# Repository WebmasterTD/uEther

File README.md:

# uEther

uEther is Ethernet exansion card designed for [Clockwork uConsole](https://www.clockworkpi.com/uconsole).

Based on the microchip LAN9500A USB 2.0 to 10/100 Ethernet Bridge.

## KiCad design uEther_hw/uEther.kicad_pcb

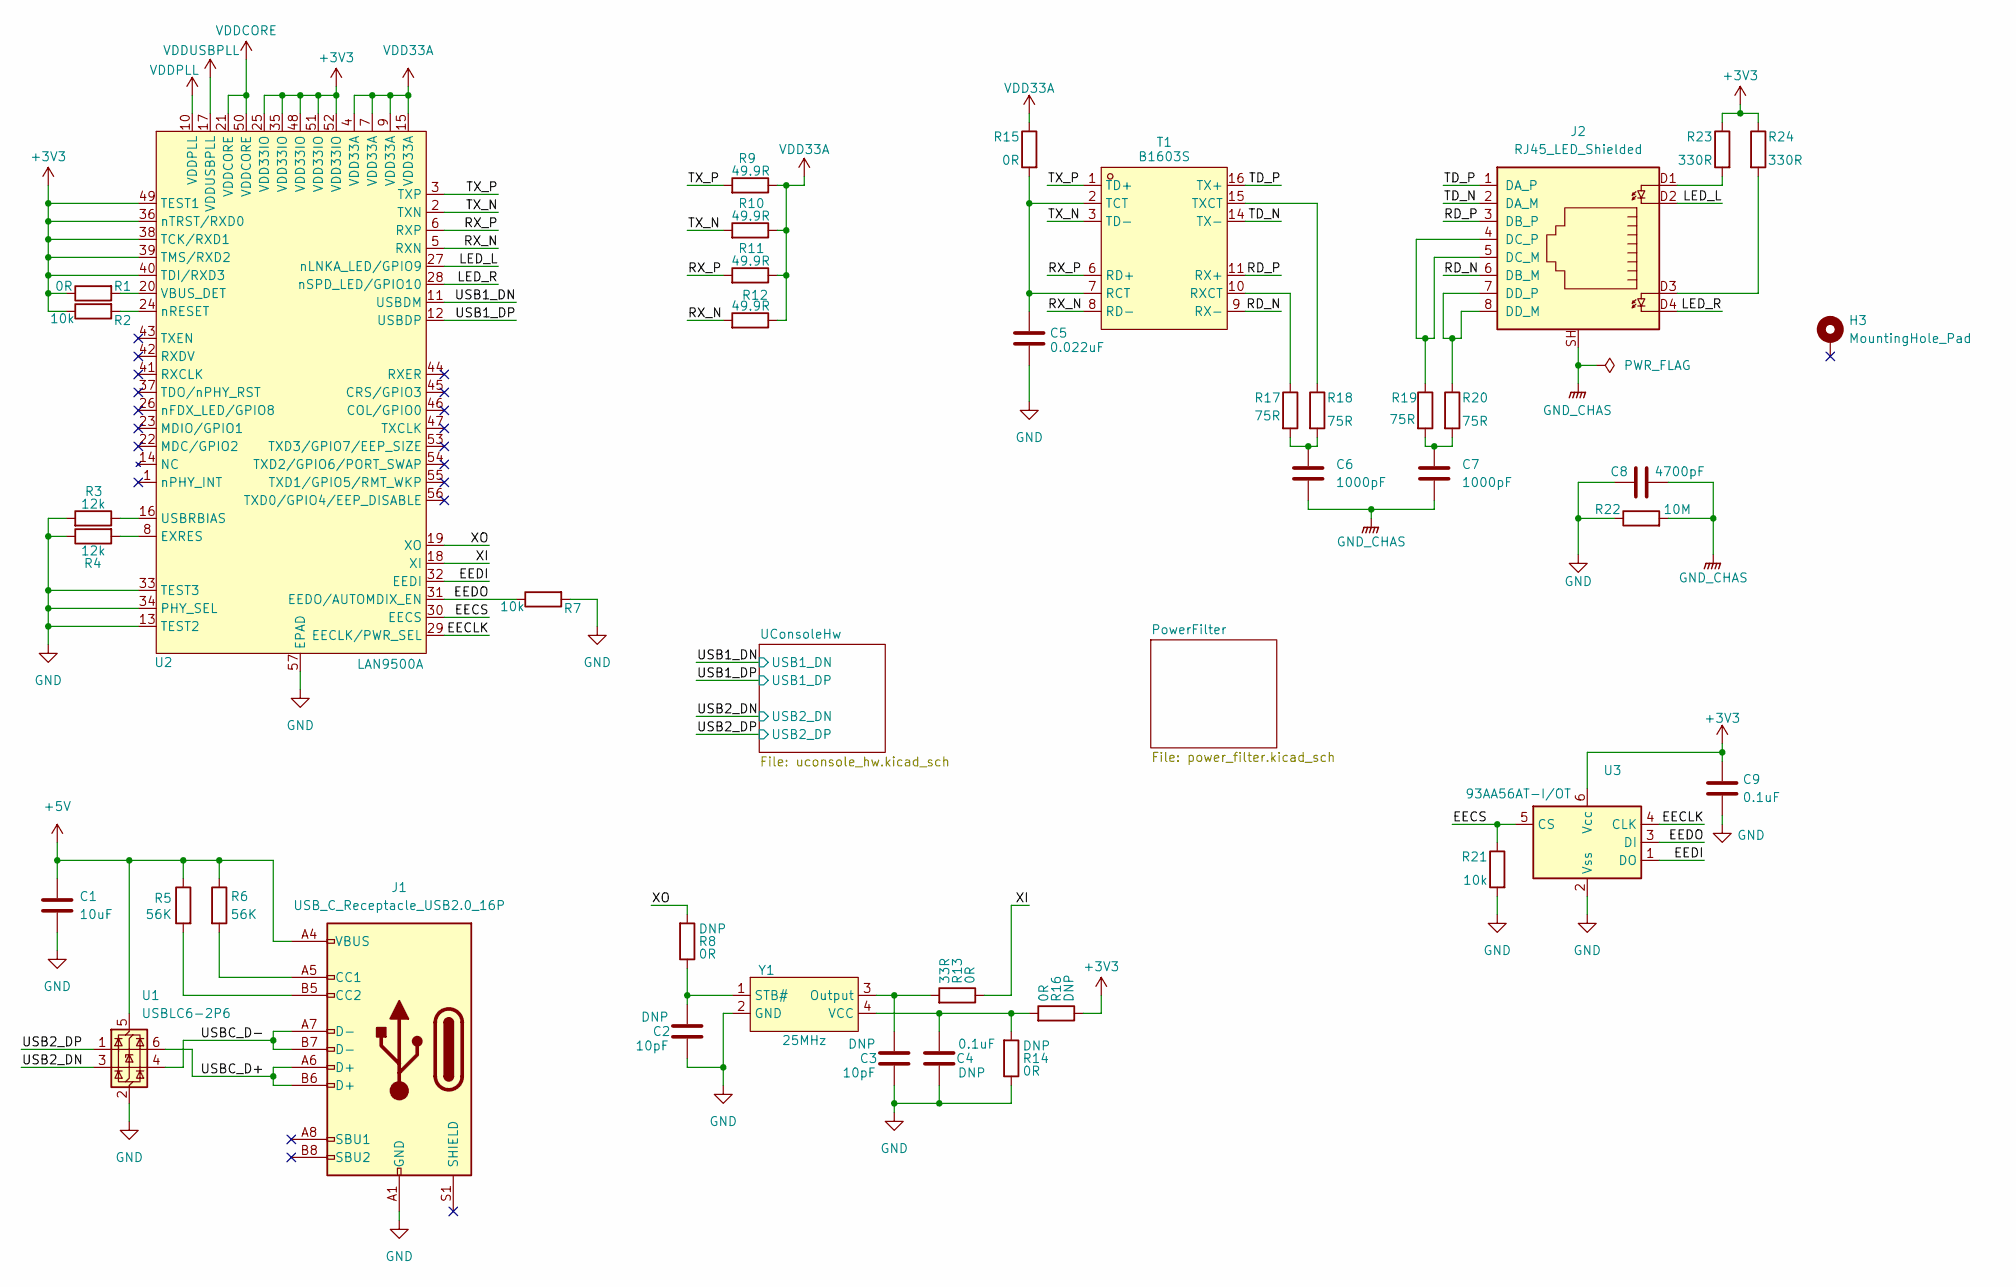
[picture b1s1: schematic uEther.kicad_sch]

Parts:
C1: 10uF; C_0603_1608Metric
C2, C3, C4: C_0603_1608Metric
C5: 0.022uF; C_0603_1608Metric
C6, C7: 1000pF; C_1206_3216Metric
C8: 4700pF; C_0603_1608Metric
C9: 0.1uF; C_0603_1608Metric
H3: MountingHole_Pad; MountingHole_2.2mm_M2_ISO7380_Pad
J1: USB_C_Receptacle_USB2.0_16P; USB_C_Receptacle_G-Switch_GT-USB-7010ASV
J2: RJ45_LED_Shielded; RJ45-005-014-11
R1, R15: 0R; R_0603_1608Metric
R2, R7, R21: 10k; R_0603_1608Metric
R3, R4: 12k; R_0603_1608Metric
R5, R6: 56K; R_0603_1608Metric
R8, R13, R14, R16: R_0603_1608Metric
R9, R10, R11, R12: 49.9R; R_0603_1608Metric
R17, R18, R19, R20: 75R; R_0603_1608Metric
R22: 10M; R_0603_1608Metric
R23, R24: 330R; R_0603_1608Metric
T1: B1603S; SOIC-16W_7.5x12.8mm_P1.27mm; Manufacturer Part B1603S; LCSC Part Name B1603S
U1: USBLC6-2P6; SOT-666
U2: LAN9500A; QFN-56-1EP_8x8mm_P0.5mm_EP5.9x5.9mm_ThermalVias; Manufacturer Part LAN9500A-ABZJ-TR; LCSC Part Name LAN950x USB 2.0 到 10/100 以太网控制器
U3: 93AA56AT-I/OT; SOT-23-6
Y1: 25MHz; Crystal_SMD_3225-4Pin_3.2x2.5mm; Manufacturer Part DSC1001CI2-025.0000T; LCSC Part Name 25MHz ±25ppm 1.8V~3.3V CMOS

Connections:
+3V3: C9.1, R1.1, R2.1, R16.1, R23.1, R24.1, U2.25 (VDD33IO), U2.35 (VDD33IO), U2.36 (nTRST/RXD0), U2.38 (TCK/RXD1), U2.39 (TMS/RXD2), U2.40 (TDI/RXD3), U2.48 (VDD33IO), U2.49 (TEST1), U2.51 (VDD33IO), U2.52 (VDD33IO), U3.6 (Vcc); also elsewhere on the board
+5V: C1.1, J1.A4 (VBUS), J1.A9 (VBUS), J1.B4 (VBUS), J1.B9 (VBUS), R5.1, R6.1, U1.5 (VBUS); also elsewhere on the board
/EECLK: U2.29 (EECLK/PWR_SEL), U3.4 (CLK)
/EECS: R21.1, U2.30 (EECS), U3.5 (CS)
/EEDI: U2.32 (EEDI), U3.1 (DO)
/EEDO: R7.1, U2.31 (EEDO/AUTOMDIX_EN), U3.3 (DI)
/LED_L: J2.D2, U2.27 (nLNKA_LED/GPIO9)
/LED_R: J2.D4, U2.28 (nSPD_LED/GPIO10)
/RD_N: J2.6 (DB_M), T1.9 (RX-)
/RD_P: J2.3 (DB_P), T1.11 (RX+)
/RX_N: R12.2, T1.8 (RD-), U2.5 (RXN)
/RX_P: R11.2, T1.6 (RD+), U2.6 (RXP)
/TD_N: J2.2 (DA_M), T1.14 (TX-)
/TD_P: J2.1 (DA_P), T1.16 (TX+)
/TX_N: R10.2, T1.3 (TD-), U2.2 (TXN)
/TX_P: R9.2, T1.1 (TD+), U2.3 (TXP)
/USB1_DN: U2.11 (USBDM); also elsewhere on the board
/USB1_DP: U2.12 (USBDP); also elsewhere on the board
/USB2_DN: U1.3 (I/O2); also elsewhere on the board
/USB2_DP: U1.1 (I/O1); also elsewhere on the board
/USBC_D+: J1.A6 (D+), J1.B6 (D+), U1.6 (I/O1)
/USBC_D-: J1.A7 (D-), J1.B7 (D-), U1.4 (I/O2)
/XI: R13.1, U2.18 (XI)
/XO: R8.2, U2.19 (XO)
GND: C1.2, C2.2, C3.2, C4.2, C5.2, C8.1, C9.2, J1.A1 (GND), J1.A12 (GND), J1.B1 (GND), J1.B12 (GND), R3.2, R4.1, R7.2, R14.1, R21.2, R22.1, U1.2 (GND), U2.13 (TEST2), U2.33 (TEST3), U2.34 (PHY_SEL), U2.57 (EPAD), U3.2 (Vss), Y1.2 (GND); also elsewhere on the board
GND_CHAS: C6.2, C7.2, C8.2, J2.SH, R22.2
unnamed: C6.1, R17.2, R18.2
unnamed: C7.1, R19.2, R20.2
unnamed: J1.A5 (CC1), R6.2
unnamed: J1.B5 (CC2), R5.2
unnamed: J2.4 (DC_P), J2.5 (DC_M), R19.1
unnamed: J2.7 (DD_P), J2.8 (DD_M), R20.1
unnamed: J2.D1, R23.2
unnamed: J2.D3, R24.2
unnamed: C5.1, R15.2, T1.2 (TCT), T1.7 (RCT)
unnamed: R17.1, T1.10 (RXCT)
unnamed: R18.1, T1.15 (TXCT)
unnamed: R4.2, U2.8 (EXRES)
unnamed: R3.1, U2.16 (USBRBIAS)
unnamed: R1.2, U2.20 (VBUS_DET)
unnamed: R2.2, U2.24 (nRESET)
unnamed: C3.1, R13.2, Y1.3 (Output)
unnamed: C2.1, R8.1, Y1.1 (STB#)
unnamed: C4.1, R14.2, R16.2, Y1.4 (VCC)
VDD33A: R9.1, R10.1, R11.1, R12.1, R15.1, U2.4 (VDD33A), U2.7 (VDD33A), U2.9 (VDD33A), U2.15 (VDD33A); also elsewhere on the board
VDDCORE: U2.21 (VDDCORE), U2.50 (VDDCORE); also elsewhere on the board
VDDPLL: U2.10 (VDDPLL); also elsewhere on the board
VDDUSBPLL: U2.17 (VDDUSBPLL); also elsewhere on the board

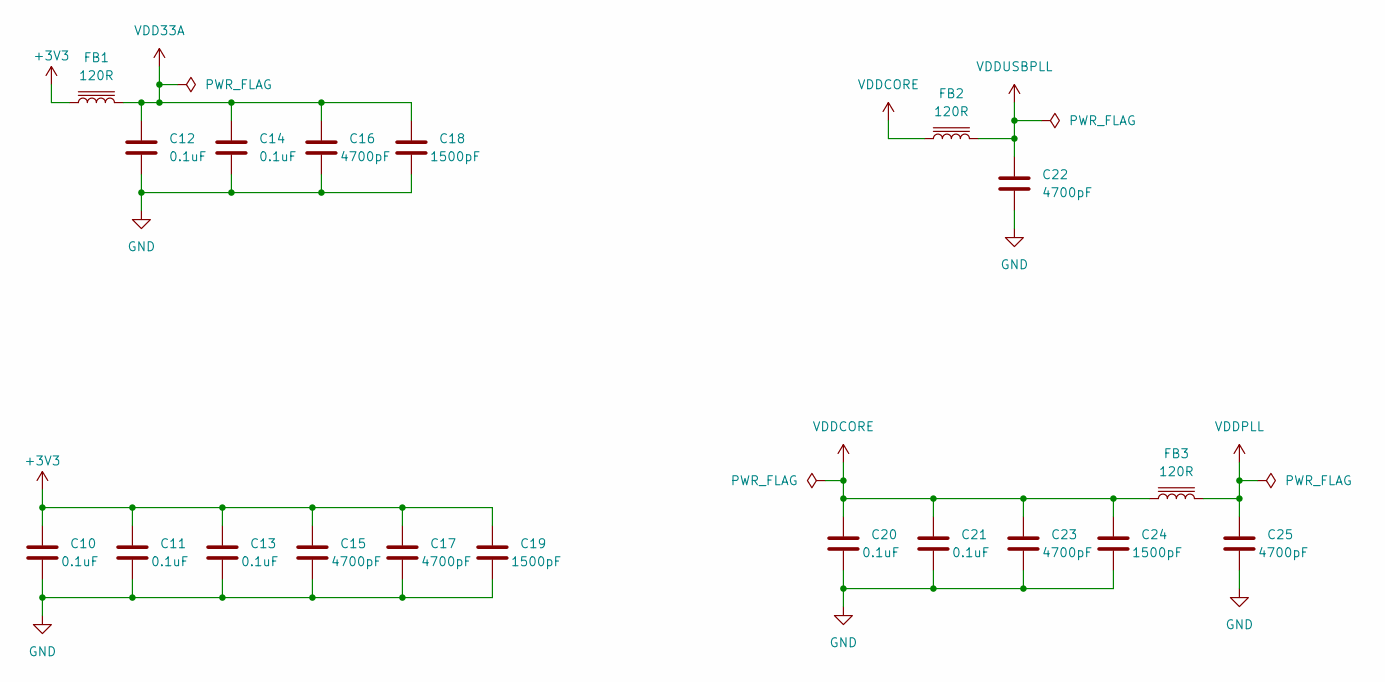
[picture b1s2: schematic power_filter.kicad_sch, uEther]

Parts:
C10, C11, C12, C13, C14, C20, C21: 0.1uF; C_0603_1608Metric
C15, C16, C17, C22, C23, C25: 4700pF; C_0603_1608Metric
C18, C19, C24: 1500pF; C_0603_1608Metric
FB1, FB2, FB3: 120R; L_0603_1608Metric

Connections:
+3V3: C10.1, C11.1, C13.1, C15.1, C17.1, C19.1, FB1.1; also elsewhere on the board
GND: C10.2, C11.2, C12.2, C13.2, C14.2, C15.2, C16.2, C17.2, C18.2, C19.2, C20.2, C21.2, C22.2, C23.2, C24.2, C25.2; also elsewhere on the board
VDD33A: C12.1, C14.1, C16.1, C18.1, FB1.2; also elsewhere on the board
VDDCORE: C20.1, C21.1, C23.1, C24.1, FB2.1, FB3.1; also elsewhere on the board
VDDPLL: C25.1, FB3.2; also elsewhere on the board
VDDUSBPLL: C22.1, FB2.2; also elsewhere on the board

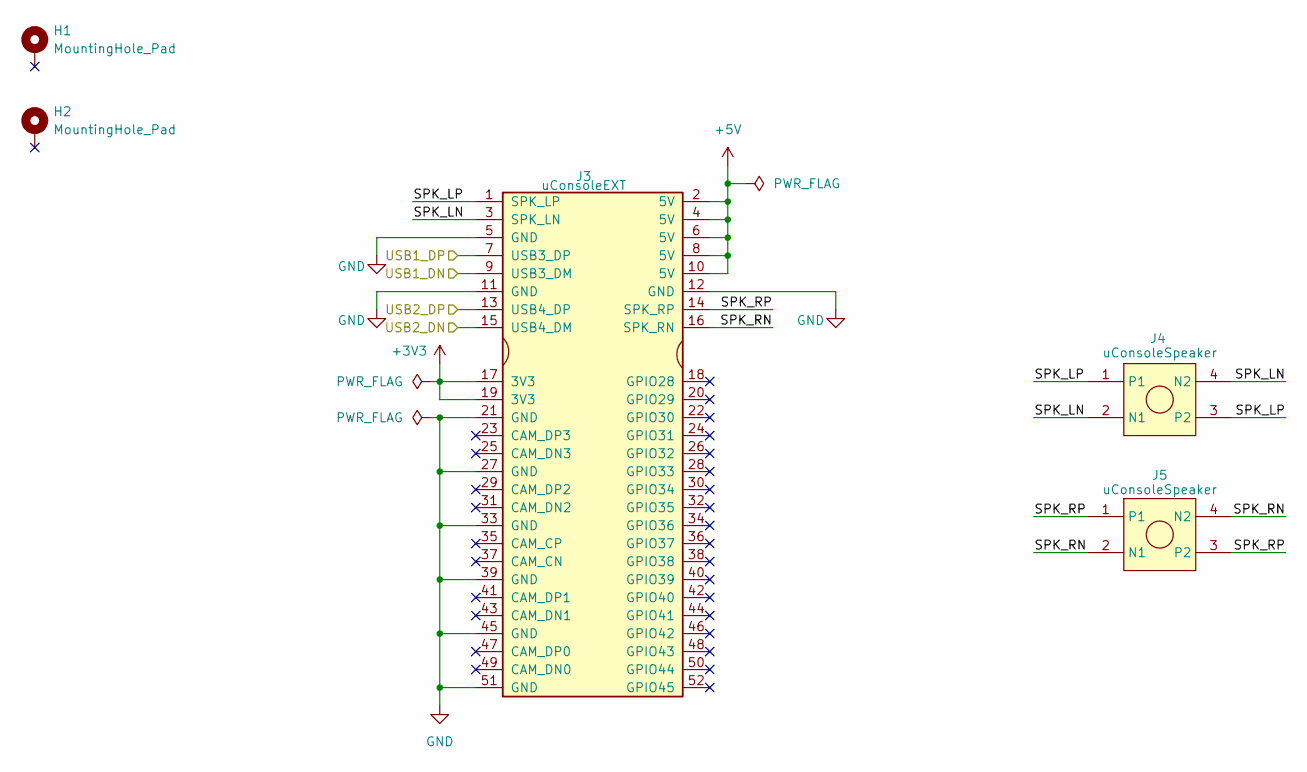
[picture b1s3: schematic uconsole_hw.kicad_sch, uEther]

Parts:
H1, H2: MountingHole_Pad; MountingHole_5mm_Pad_TopOnly
J3: uConsoleEXT; ext
J4, J5: uConsoleSpeaker; speaker

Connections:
+3V3: J3.17 (3V3), J3.19 (3V3); also elsewhere on the board
+5V: J3.2 (5V), J3.4 (5V), J3.6 (5V), J3.8 (5V), J3.10 (5V); also elsewhere on the board
/UConsoleHw/SPK_LN: J3.3 (SPK_LN), J4.2 (N1), J4.4 (N2)
/UConsoleHw/SPK_LP: J3.1 (SPK_LP), J4.1, J4.3 (P2)
/UConsoleHw/SPK_RN: J3.16 (SPK_RN), J5.2 (N1), J5.4 (N2)
/UConsoleHw/SPK_RP: J3.14 (SPK_RP), J5.1, J5.3 (P2)
/USB1_DN: J3.9 (USB3_DM); also elsewhere on the board
/USB1_DP: J3.7 (USB3_DP); also elsewhere on the board
/USB2_DN: J3.15 (USB4_DM); also elsewhere on the board
/USB2_DP: J3.13 (USB4_DP); also elsewhere on the board
GND: J3.5 (GND), J3.11 (GND), J3.12 (GND), J3.21 (GND), J3.27 (GND), J3.33 (GND), J3.39 (GND), J3.45 (GND), J3.51 (GND); also elsewhere on the board

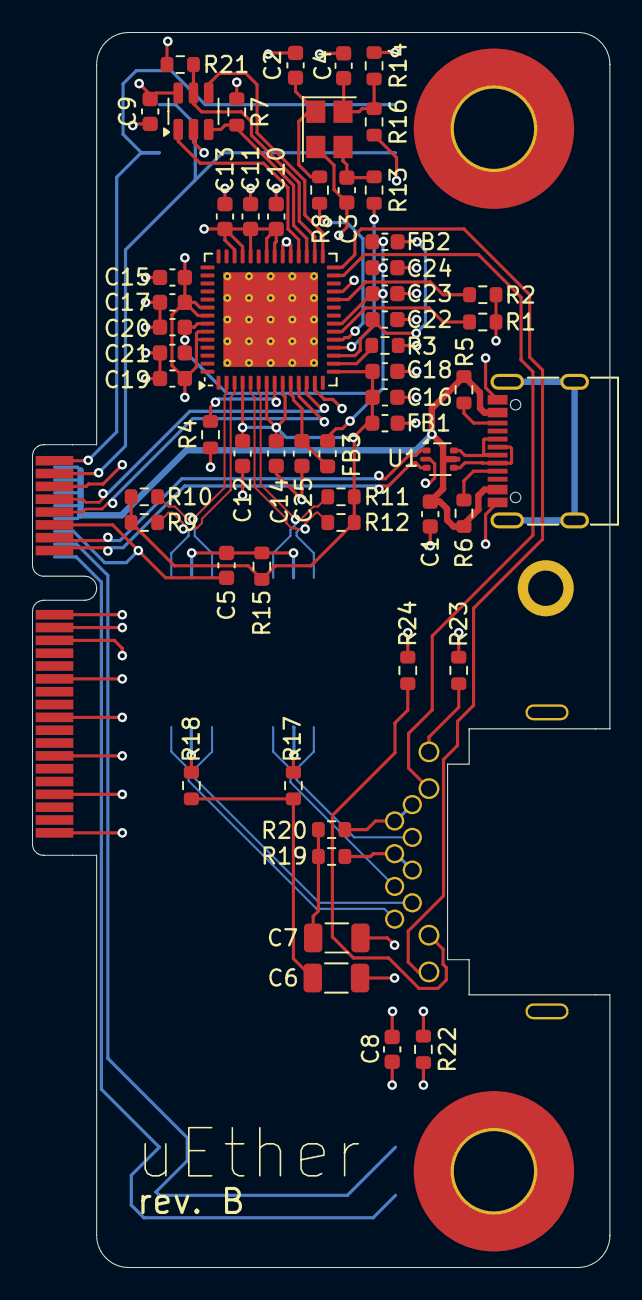
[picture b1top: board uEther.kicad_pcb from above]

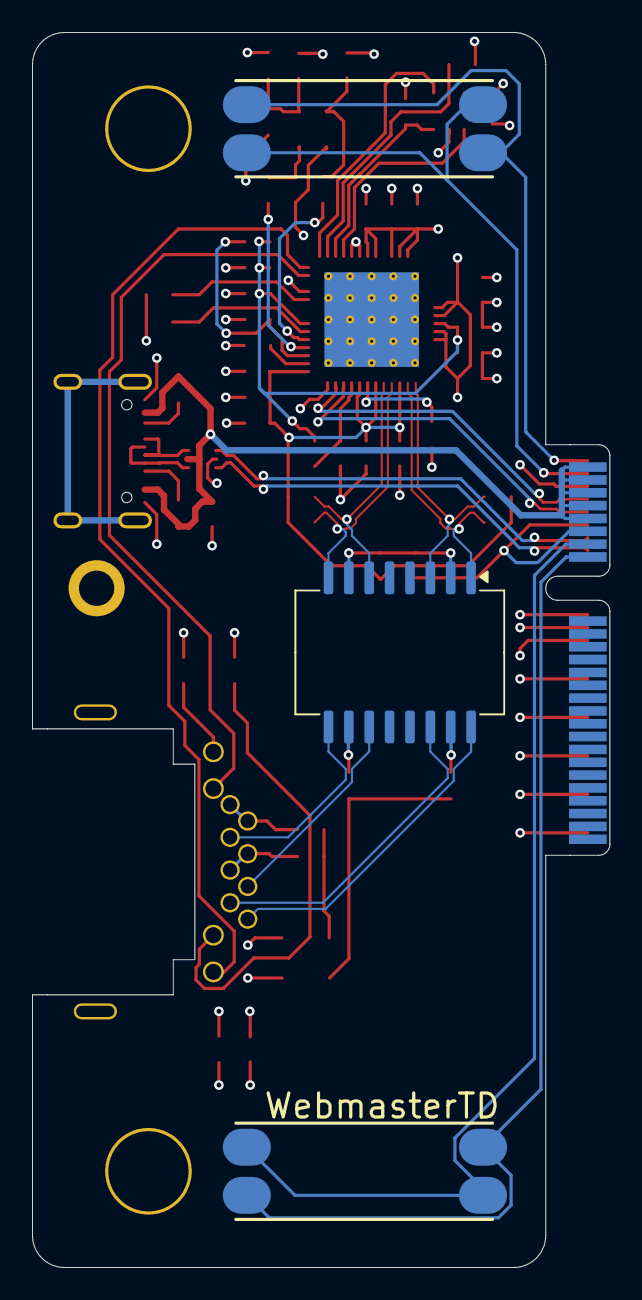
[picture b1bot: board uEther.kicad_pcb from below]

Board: 4 copper layers, 36.0 x 77.0 mm, 65 parts (4 on the bottom side), 52 nets.

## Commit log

2025-04-03 changed print profile
2025-04-11 Changed Schematic
2025-04-12 Schematic for rev B
2025-04-13 reworked PCB
2025-04-16 design rev B
2025-04-27 updated 3D files
2025-06-16 Updated 3D files files
